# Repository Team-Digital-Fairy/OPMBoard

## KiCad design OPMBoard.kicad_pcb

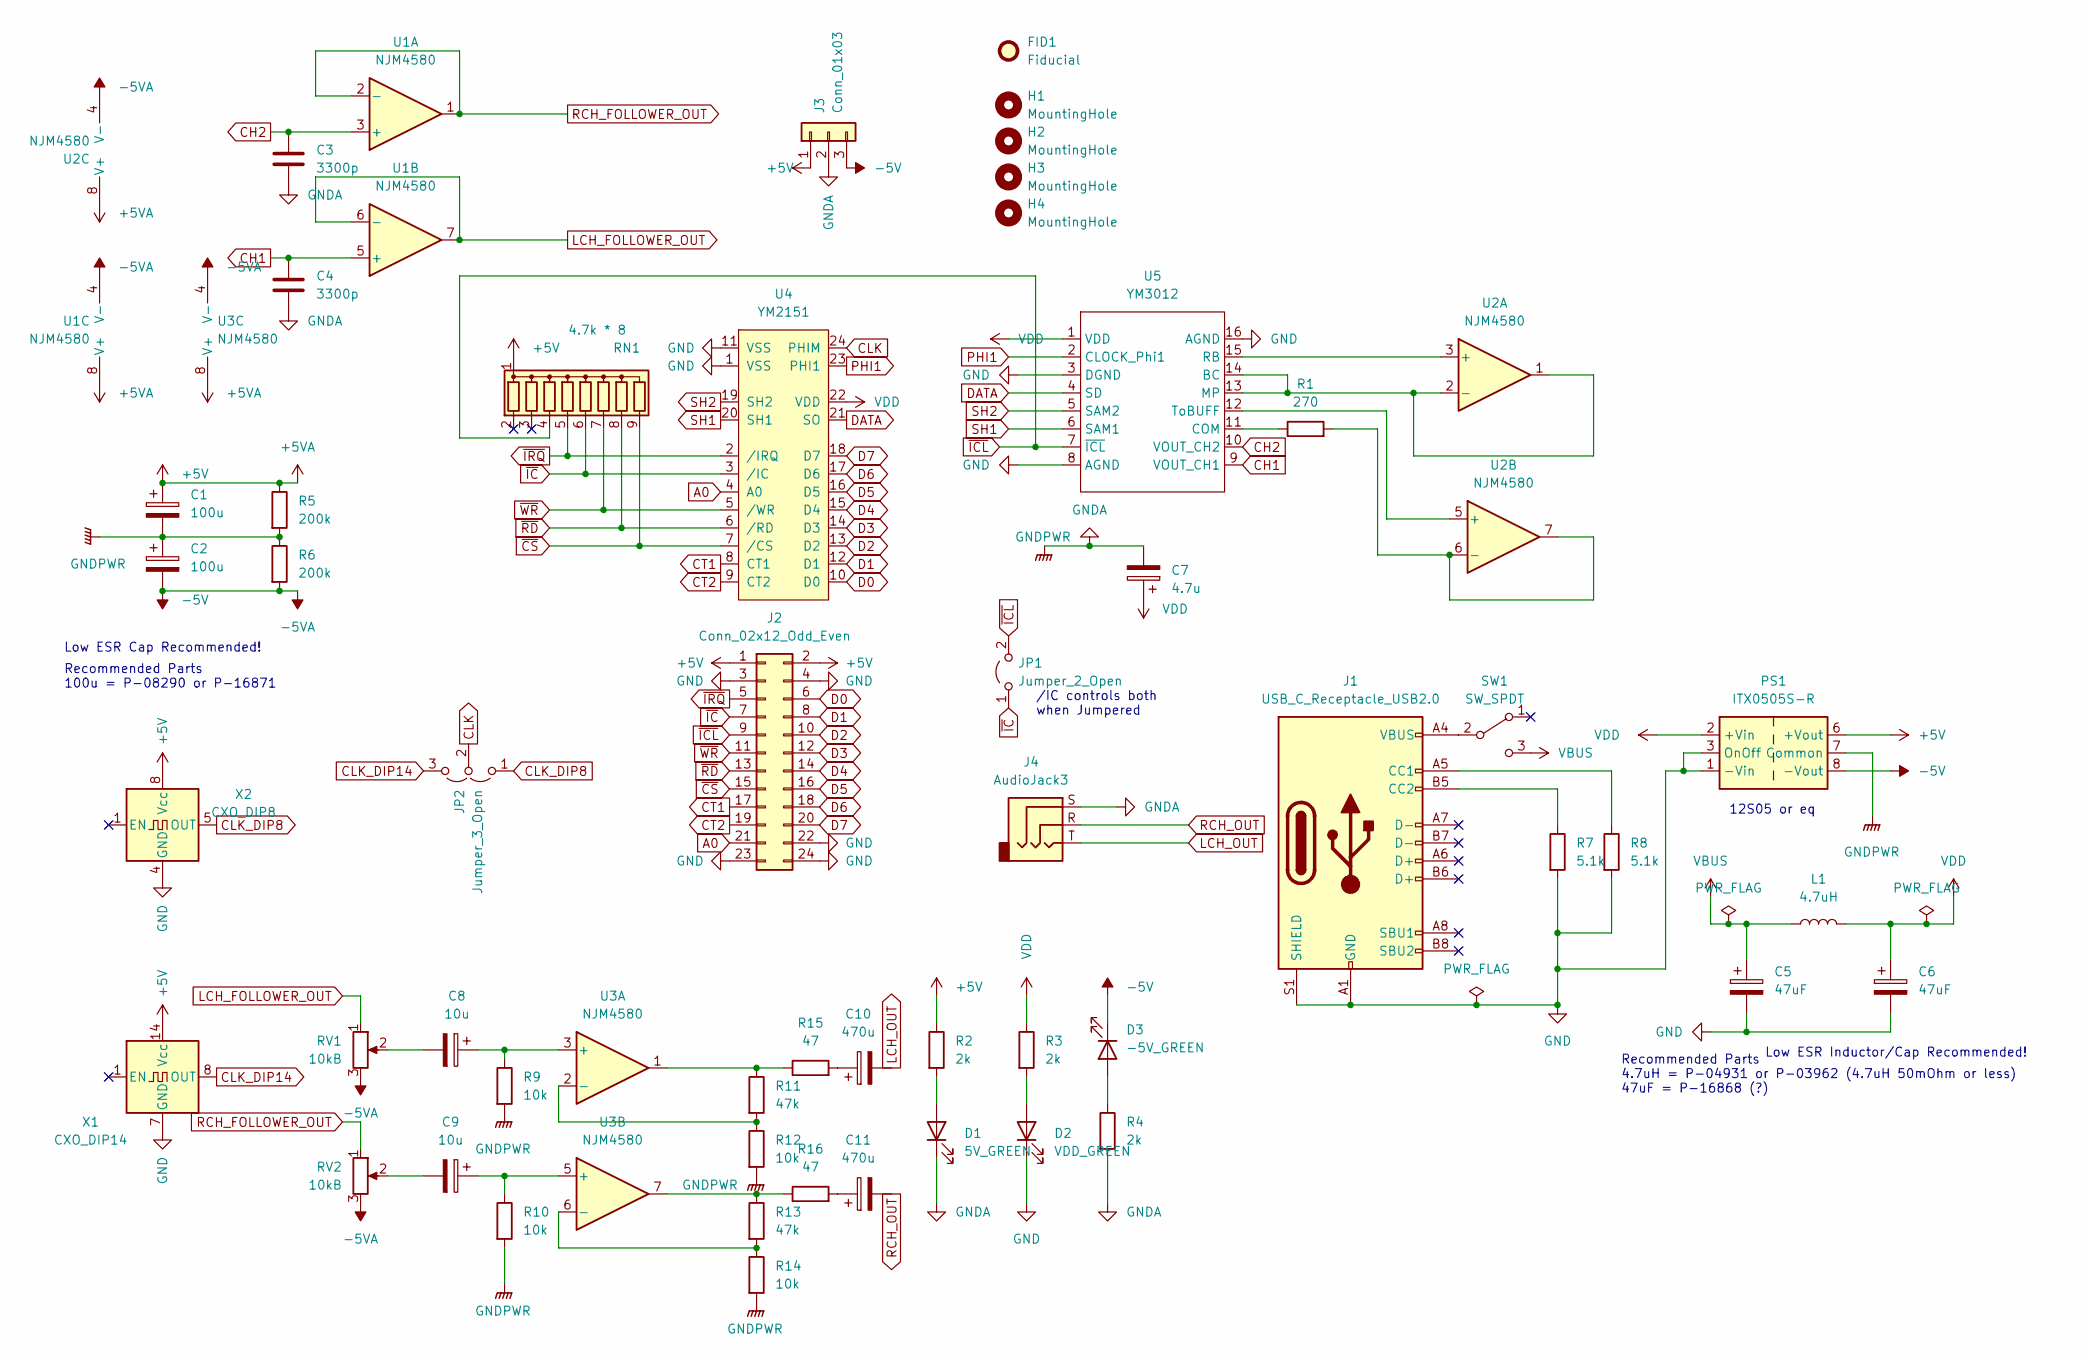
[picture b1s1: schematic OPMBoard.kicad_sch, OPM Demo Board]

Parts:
C1, C2: 100u; CP_Radial_D6.3mm_P2.50mm
C3, C4: 3300p; C_Disc_D5.0mm_W2.5mm_P5.00mm
C5, C6: 47uF; CP_Radial_D5.0mm_P2.50mm
C7: 4.7u; CP_Radial_D5.0mm_P2.50mm
C8, C9: 10u; CP_Radial_D5.0mm_P2.50mm
C10, C11: 470u; CP_Radial_D5.0mm_P2.00mm
D1: 5V_GREEN; LED_D5.0mm
D2: VDD_GREEN; LED_D5.0mm
D3: -5V_GREEN; LED_D5.0mm
FID1: Fiducial; Fiducial_0.5mm_Mask1mm
H1, H2, H3, H4: MountingHole; MountingHole_3.2mm_M3
J1: USB_C_Receptacle_USB2.0; USB_C_Receptacle_HRO_TYPE-C-31-M-12
J2: Conn_02x12_Odd_Even; PinHeader_2x12_P2.54mm_Vertical
J3: Conn_01x03; PinSocket_1x03_P2.54mm_Vertical
J4: AudioJack3; Jack_3.5mm_Lumberg_1503_07_Horizontal
JP1: Jumper_2_Open; PinHeader_1x02_P2.54mm_Vertical
JP2: Jumper_3_Open; PinHeader_1x03_P2.54mm_Vertical
L1: 4.7uH; L_Axial_L7.0mm_D3.3mm_P12.70mm_Horizontal_Fastron_MICC
PS1: ITX0505S-R; Converter_DCDC_XP_POWER-ITxxxxxS_THT
R1: 270; R_Axial_DIN0207_L6.3mm_D2.5mm_P10.16mm_Horizontal
R2, R3, R4: 2k; R_Axial_DIN0207_L6.3mm_D2.5mm_P10.16mm_Horizontal
R5, R6: 200k; R_Axial_DIN0207_L6.3mm_D2.5mm_P10.16mm_Horizontal
R7, R8: 5.1k; R_Axial_DIN0207_L6.3mm_D2.5mm_P10.16mm_Horizontal
R9, R10, R12, R14: 10k; R_Axial_DIN0207_L6.3mm_D2.5mm_P10.16mm_Horizontal
R11, R13: 47k; R_Axial_DIN0207_L6.3mm_D2.5mm_P10.16mm_Horizontal
R15, R16: 47; R_Axial_DIN0207_L6.3mm_D2.5mm_P10.16mm_Horizontal
RN1: 4.7k * 8; R_Array_SIP9
RV1, RV2: 10kB; Potentiometer_Bourns_3386P_Vertical
SW1: SW_SPDT; SW_Slide_1P2T_CK_OS102011MS2Q
U1, U2, U3: NJM4580; DIP-8_W7.62mm_Socket_LongPads
U4: YM2151; DIP-24_W15.24mm_Socket_LongPads
U5: YM3012; DIP-16_W7.62mm_Socket_LongPads
X1: CXO_DIP14; Oscillator_DIP-14_Full
X2: CXO_DIP8; Oscillator_DIP-8_Full

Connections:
+5V: C1.1, C7.1, J2.1, J2.2, J3.1, PS1.6 (+Vout), R2.1, R5.1, RN1.1 (common), U1.8 (V+), U2.8 (V+), U3.8 (V+), U4.22 (VDD), U5.1 (VDD), X1.14 (Vcc), X2.8 (Vcc)
-5V: C2.2, D3.1 (K), J3.3, PS1.8 (-Vout), R6.2, RV1.3, RV2.3, U1.4 (V-), U2.4 (V-), U3.4 (V-)
A0: J2.21, U4.4 (A0)
CH1: C4.1, U1.5 (+), U5.9 (VOUT_CH1)
CH2: C3.1, U1.3 (+), U5.10 (VOUT_CH2)
CLK: JP2.2 (C), U4.24 (PHIM)
CLK_DIP8: JP2.1 (A), X2.5 (OUT)
CLK_DIP14: JP2.3 (B), X1.8 (OUT)
CT1: J2.17, U4.8 (CT1)
CT2: J2.19, U4.9 (CT2)
D0: J2.6, U4.10 (D0)
D1: J2.8, U4.12 (D1)
D2: J2.10, U4.13 (D2)
D3: J2.12, U4.14 (D3)
D4: J2.14, U4.15 (D4)
D5: J2.16, U4.16 (D5)
D6: J2.18, U4.17 (D6)
D7: J2.20, U4.18 (D7)
DATA: U4.21 (SO), U5.4 (SD)
GND: C5.2, C6.2, D2.1 (K), J1.A1 (GND), J1.A12 (GND), J1.B1 (GND), J1.B12 (GND), J1.S1 (SHIELD), J2.3, J2.4, J2.22, J2.23, J2.24, PS1.1 (-Vin), PS1.3 (OnOff), R7.2, R8.2, U4.1 (VSS), U4.11 (VSS), U5.3 (DGND), U5.8 (AGND), U5.16 (AGND), X1.7 (GND), X2.4 (GND)
GNDA: C1.2, C2.1, C3.2, C4.2, C7.2, D1.1 (K), J3.2, J4.S, PS1.7 (Common), R4.2, R5.2, R6.1, R9.2, R10.2, R12.2, R14.2
LCH_FOLLOWER_OUT: RV1.1, U1.6 (-), U1.7
LCH_OUT: C10.2, J4.T
unnamed: C8.1, R9.1, U3.3 (+)
unnamed: C8.2, RV1.2
unnamed: C9.1, R10.1, U3.5 (+)
unnamed: C9.2, RV2.2
unnamed: C10.1, R15.2
unnamed: C11.1, R16.2
unnamed: D1.2 (A), R2.2
unnamed: D2.2 (A), R3.2
unnamed: D3.2 (A), R4.1
unnamed: J1.A4 (VBUS), J1.A9 (VBUS), J1.B4 (VBUS), J1.B9 (VBUS), SW1.2 (B)
unnamed: J1.A5 (CC1), R8.1
unnamed: J1.B5 (CC2), R7.1
unnamed: R1.1, U5.11 (COM)
unnamed: R1.2, U2.6 (-), U2.7
unnamed: R11.1, R15.1, U3.1
unnamed: R11.2, R12.1, U3.2 (-)
unnamed: R13.1, R16.1, U3.7
unnamed: R13.2, R14.1, U3.6 (-)
unnamed: U2.1, U2.2 (-), U5.13 (MP), U5.14 (BC)
unnamed: U2.3 (+), U5.15 (RB)
unnamed: U2.5 (+), U5.12 (ToBUFF)
PHI1: U4.23 (PHI1), U5.2 (CLOCK_Phi1)
RCH_FOLLOWER_OUT: RV2.1, U1.1, U1.2 (-)
RCH_OUT: C11.2, J4.R
SH1: U4.20 (SH1), U5.6 (SAM1)
SH2: U4.19 (SH2), U5.5 (SAM2)
VBUS: C5.1, L1.1, SW1.3 (C)
VDD: C6.1, L1.2, PS1.2 (+Vin), R3.1
~CS: J2.15, RN1.9 (R8), U4.7 (/CS)
~ICL: J2.9, JP1.2 (B), RN1.4 (R3), U5.7 (~ICL)
~IC: J2.7, JP1.1 (A), RN1.6 (R5), U4.3 (/IC)
~IRQ: J2.5, RN1.5 (R4), U4.2 (/IRQ)
~RD: J2.13, RN1.8 (R7), U4.6 (/RD)
~WR: J2.11, RN1.7 (R6), U4.5 (/WR)

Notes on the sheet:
Recommended Parts 4.7uH = P-04931 or P-03962 (4.7uH 50mOhm or less) 47uF = P-16868 (?)
Recommended Parts 100u = P-08290 or P-16871
/IC controls both when Jumpered
12S05 or eq
Low ESR Inductor/Cap Recommended!
Low ESR Cap Recommended!

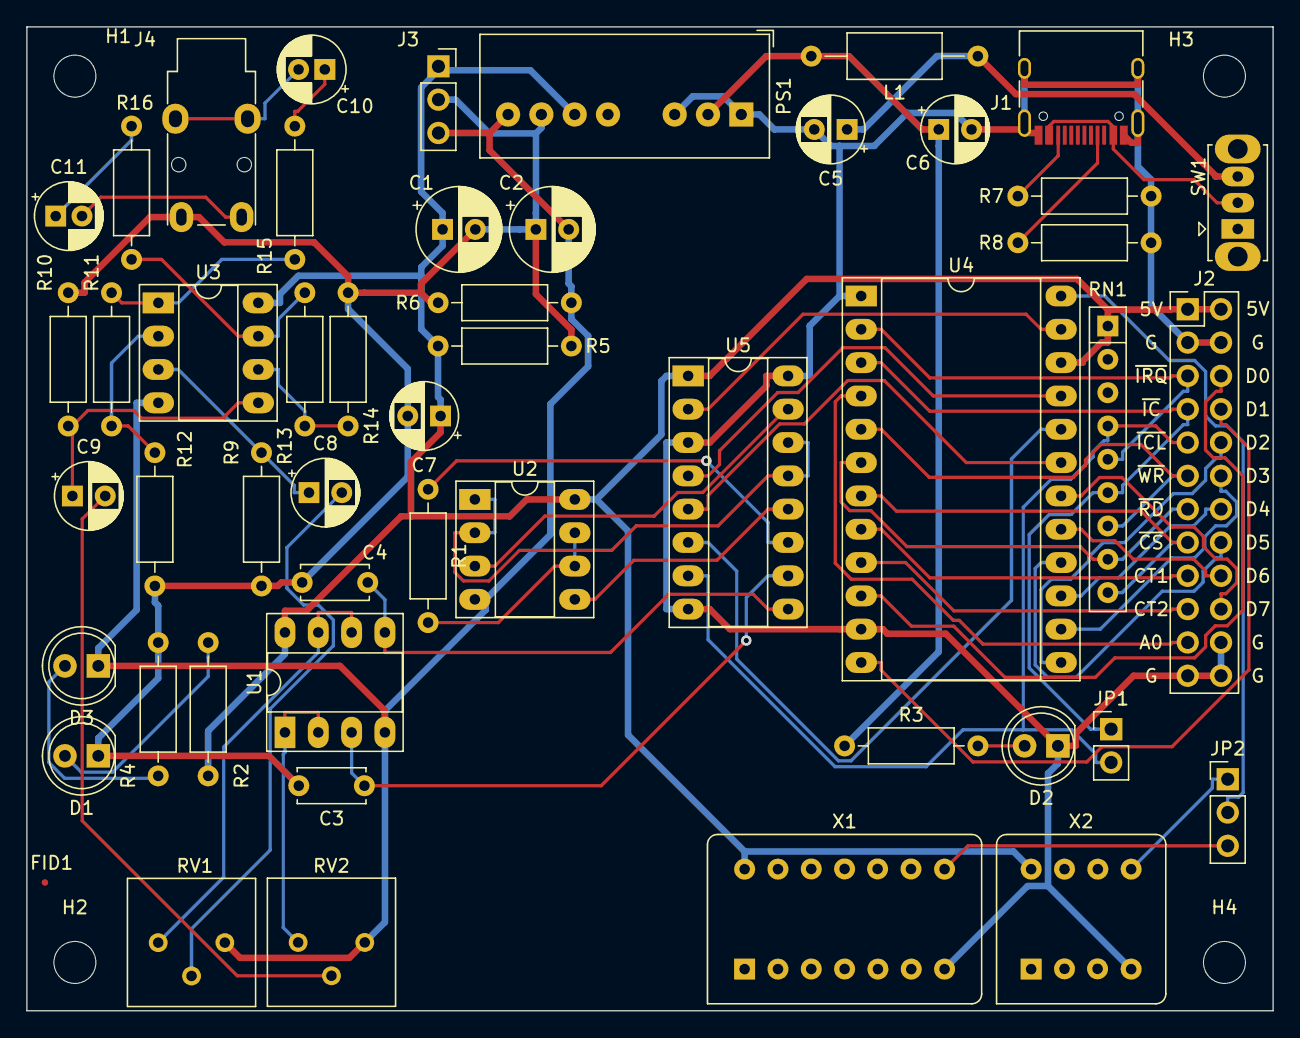
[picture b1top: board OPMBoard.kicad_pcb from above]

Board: 2 copper layers, 95.0 x 75.0 mm, 54 parts (0 on the bottom side), 57 nets.

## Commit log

2022-10-05 Update schematic
